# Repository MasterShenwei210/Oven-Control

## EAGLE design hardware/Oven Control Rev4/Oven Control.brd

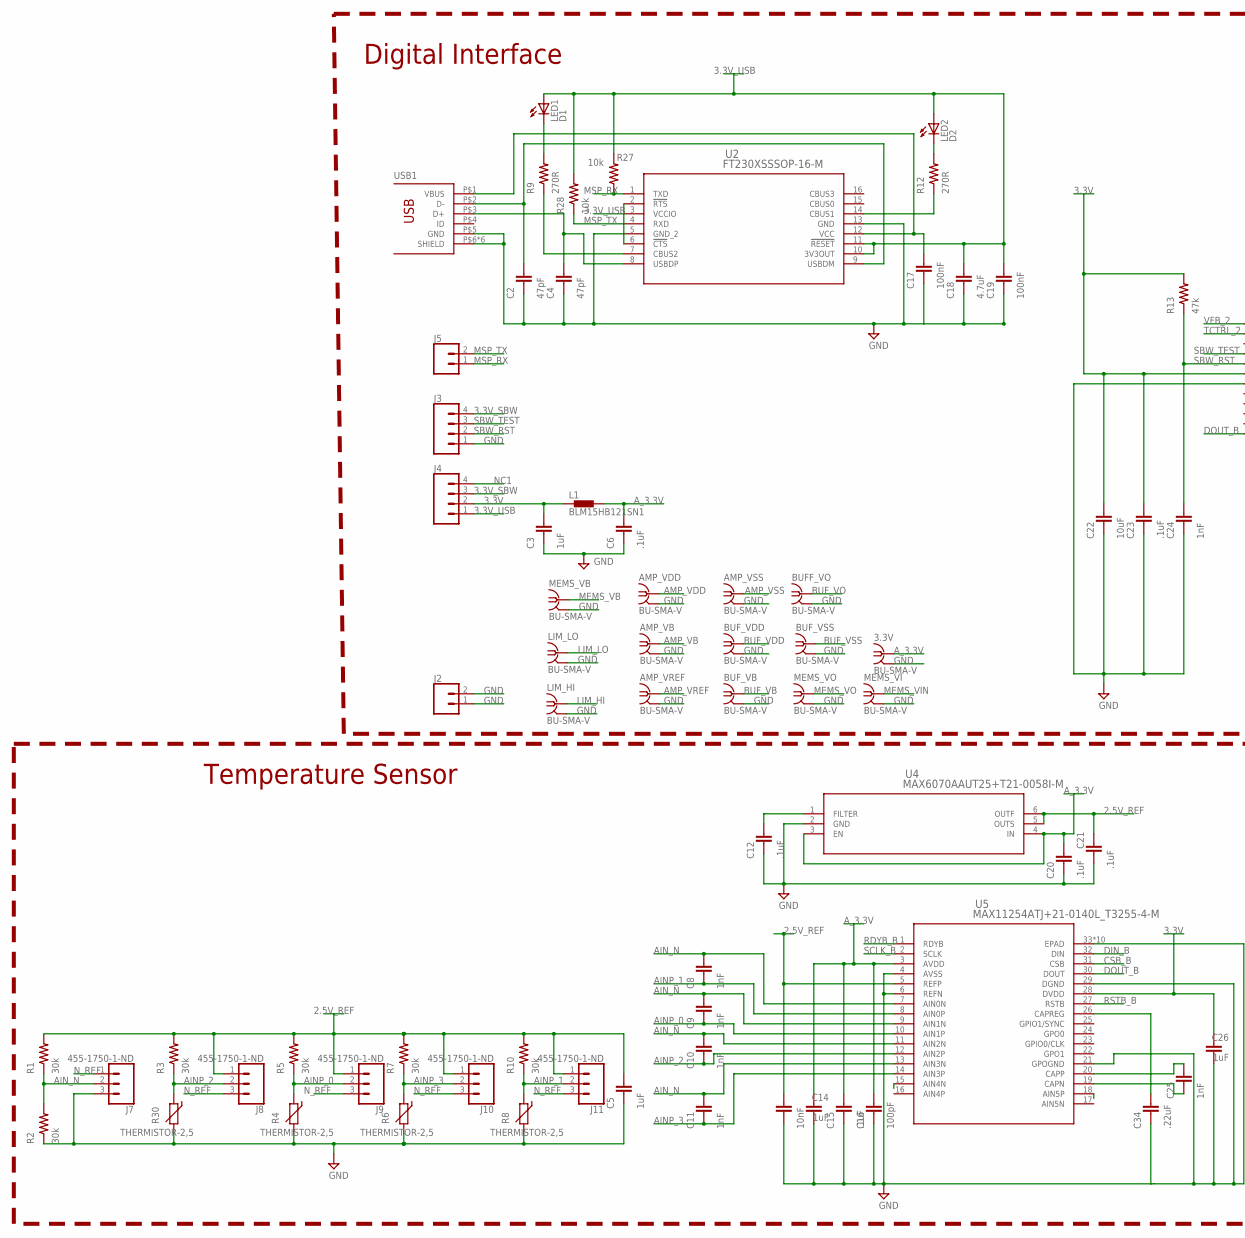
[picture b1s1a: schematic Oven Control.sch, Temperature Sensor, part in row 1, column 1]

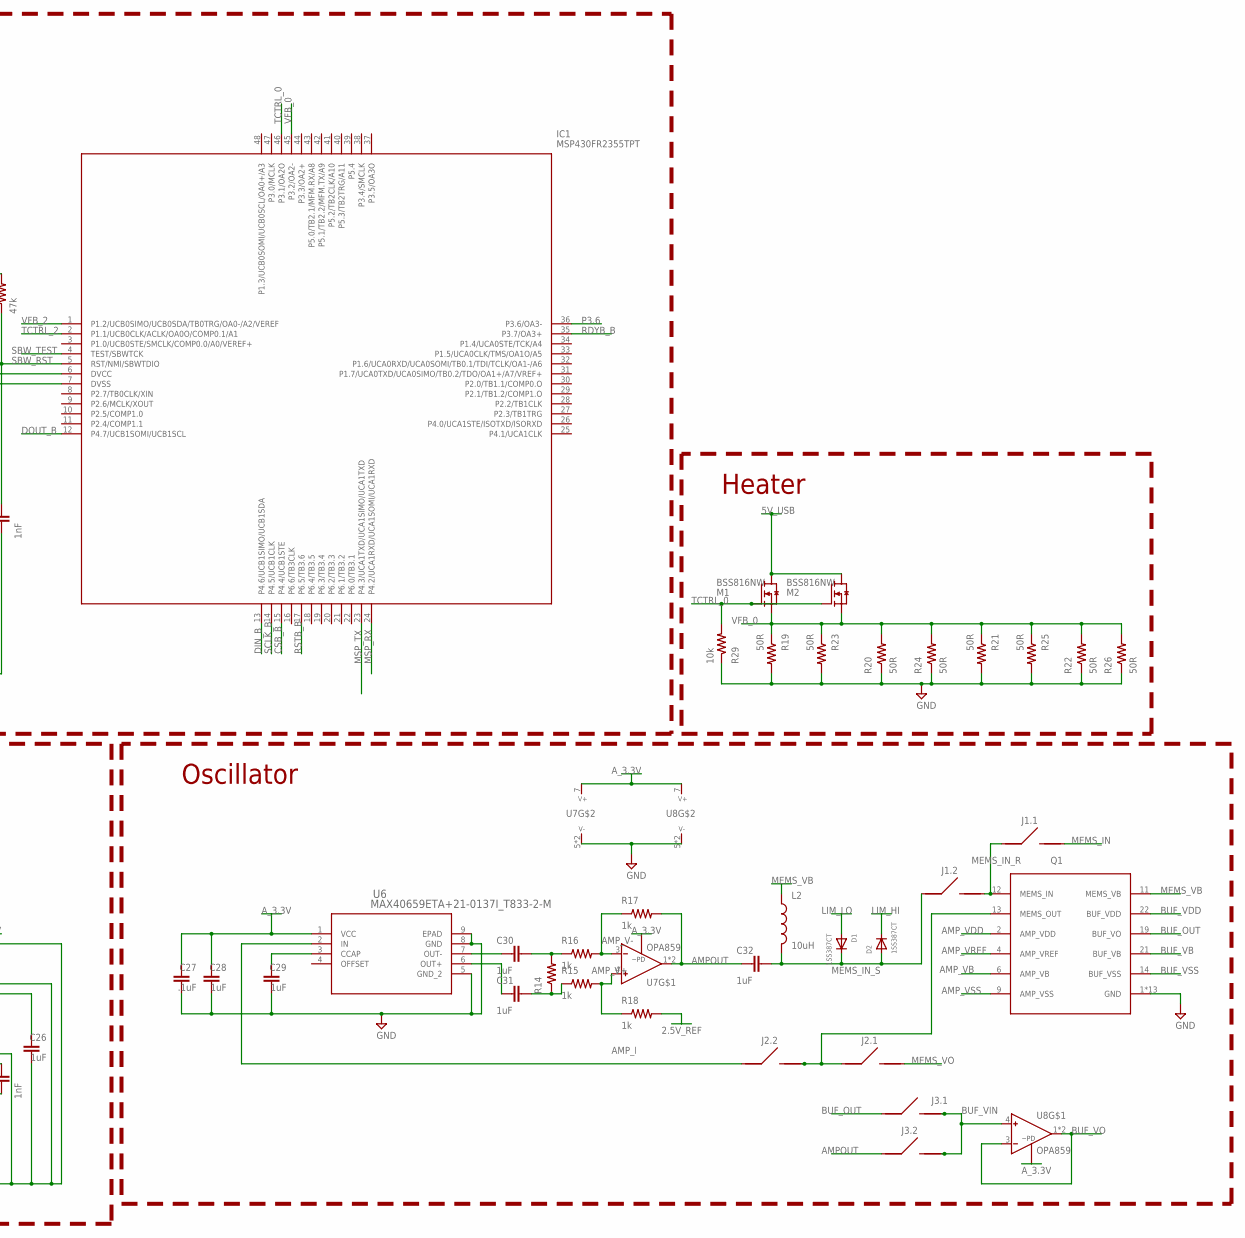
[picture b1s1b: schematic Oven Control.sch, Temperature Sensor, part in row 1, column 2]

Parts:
3.3V: BU-SMA-V
AMP_VB: BU-SMA-V
AMP_VDD: BU-SMA-V
AMP_VREF: BU-SMA-V
AMP_VSS: BU-SMA-V
BUFF_VO: BU-SMA-V
BUF_VB: BU-SMA-V
BUF_VDD: BU-SMA-V
BUF_VSS: BU-SMA-V
C2, C4: 47pF; 0402-CAP
C3, C5, C14, C26, C28, C29, C30, C31, C32: 1uF; 0402-CAP
C6, C12, C15, C20, C21, C23, C27: .1uF; 0402-CAP
C8, C9, C10, C11, C24, C25: 1nF; 0402-CAP
C13: 10nF; 0402-CAP
C16: 100pF; 0402-CAP
C17, C19: 100nF; 0402-CAP
C18: 4.7uF; 0402-CAP
C22: 10uF; 0603-CAP
C34: .22uF; 0402-CAP
D1, D2: 1SS387CT; SOD-882
IC1: MSP430FR2355TPT; QFP50P900X900X145-48N
J1.1, J1.2, J2.1, J2.2, J3.1, J3.2: 0OHM_R; R0402
J2, J5: CONN_02; 1X02
J3, J4: CONN_04; 1X04
J7, J8, J9, J10, J11: 455-1750-1-ND; 1X03
L1: BLM15HB121SN1; 0402
L2: 10uH; R0805
LED1: D1; CHIPLED_0603
LED2: D2; CHIPLED_0603
LIM_HI: BU-SMA-V
LIM_LO: BU-SMA-V
M1, M2: BSS816NW; SOT-323
MEMS_VB: BU-SMA-V
MEMS_VI: BU-SMA-V
MEMS_VO: BU-SMA-V
Q1: MEMS_RESONATOR; DIL24
R1, R2, R3, R5, R7, R10: 30k; R0603
R4, R6, R8, R30: THERMISTOR-2,5; RS-2,5; PART_NO NXRT15WB473FA1B030
R9, R12: 270R; R0603
R13: 47k; R0603
R14: 150R; R0402
R15, R16, R17, R18: 1k; R0402
R19, R20, R21, R22, R23, R24, R25, R26: 50R; R1206
R27, R28, R29: 10k; R0402
U2: FT230XSSSOP-16-M; SSOP-16-M
U4: MAX6070AAUT25+T21-0058I-M; 21-0058I-M
U5: MAX11254ATJ+21-0140L_T3255-4-M; 21-0140L_T3255-4-M
U6: MAX40659ETA+21-0137I_T833-2-M; 21-0137I_T833-2-M
U7, U8: OPA859; SON50P200X200X80-9N
USB1: USB-OTGMICRO-AB; USB-MICRO-AB

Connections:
2.5V_REF: C5.2, C13.2, C21.2, J8.1, J9.1, J10.1, J11.1, R1.2, R3.2, R5.2, R7.2, R10.2, R18.2, U4.5 (OUTS), U4.6 (OUTF), U5.5 (REFP)
3.3V: C3.2, C22.2, C23.2, C26.2, IC1.6 (DVCC), J4.2, L1.1, R13.2, U5.28 (DVDD)
3.3V_SBW: J3.4, J4.3
3.3V_USB: C18.2, C19.2, J4.1, LED1.A, LED2.A, R27.2, R28.2, U2.3 (VCCIO), U2.10 (3V3OUT), U2.11 (!RESET)
5V_USB: C17.2, M1.D, M2.D, U2.12 (VCC), USB1.P$1 (VBUS)
AINP_0: C9.1, J9.2, R4.1, R5.1, U5.10 (AIN1P)
AINP_1: C8.1, J11.2, R8.1, R10.1, U5.8 (AIN0P)
AINP_2: C10.1, J8.2, R3.1, R30.1, U5.12 (AIN2P)
AINP_3: C11.1, J10.2, R6.1, R7.1, U5.14 (AIN3P)
AIN_N: C8.2, C9.2, C10.2, C11.2, J7.2, R1.1, R2.2, U5.7 (AIN0N), U5.9 (AIN1N), U5.11 (AIN2N), U5.13 (AIN3N)
AMPOUT: C32.1, J3.2.1, R17.2, U7.1 (OUT), U7.6 (OUT)
AMP_I: J2.2.1, U6.2 (IN)
AMP_V+: R15.2, R18.1, U7.4 (IN+)
AMP_V-: R16.2, R17.1, U7.3 (IN-)
AMP_VB: AMP_VB.1, Q1.6 (AMP_VB)
AMP_VDD: AMP_VDD.1, Q1.2 (AMP_VDD)
AMP_VREF: AMP_VREF.1, Q1.4 (AMP_VREF)
AMP_VSS: AMP_VSS.1, Q1.9 (AMP_VSS)
A_3.3V: 3.3V.1, C6.2, C14.2, C15.2, C16.2, C20.2, C27.2, C28.2, L1.2, U4.3 (EN), U4.4 (IN), U5.3 (AVDD), U6.1 (VCC), U7.7 (V+), U7.8, U8.7 (V+), U8.8
BUF_OUT: J3.1.1, Q1.19 (BUF_VO)
BUF_VB: BUF_VB.1, Q1.21 (BUF_VB)
BUF_VDD: BUF_VDD.1, Q1.22 (BUF_VDD)
BUF_VIN: J3.1.2, J3.2.2, U8.4 (IN+)
BUF_VO: BUFF_VO.1, U8.1 (OUT), U8.3 (IN-), U8.6 (OUT)
BUF_VSS: BUF_VSS.1, Q1.14 (BUF_VSS)
CSB_B: IC1.15 (P4.4/UCB1STE), U5.31 (CSB)
D+: C4.2, U2.8 (USBDP), USB1.P$3 (D+)
D-: C2.2, U2.9 (USBDM), USB1.P$2 (D-)
DIN_B: IC1.13 (P4.6/UCB1SIMO/UCB1SDA), U5.32 (DIN)
DOUT_B: IC1.12 (P4.7/UCB1SOMI/UCB1SCL), U5.30 (DOUT)
GND: 3.3V.2, 3.3V.3 (2), 3.3V.4 (2), 3.3V.5 (2), AMP_VB.2, AMP_VB.3 (2), AMP_VB.4 (2), AMP_VB.5 (2), AMP_VDD.2, AMP_VDD.3 (2), AMP_VDD.4 (2), AMP_VDD.5 (2), AMP_VREF.2, AMP_VREF.3 (2), AMP_VREF.4 (2), AMP_VREF.5 (2), AMP_VSS.2, AMP_VSS.3 (2), AMP_VSS.4 (2), AMP_VSS.5 (2), BUFF_VO.2, BUFF_VO.3 (2), BUFF_VO.4 (2), BUFF_VO.5 (2), BUF_VB.2, BUF_VB.3 (2), BUF_VB.4 (2), BUF_VB.5 (2), BUF_VDD.2, BUF_VDD.3 (2), BUF_VDD.4 (2), BUF_VDD.5 (2), BUF_VSS.2, BUF_VSS.3 (2), BUF_VSS.4 (2), BUF_VSS.5 (2), C2.1, C3.1, C4.1, C5.1, C6.1, C12.1, C13.1, C14.1, C15.1, C16.1, C17.1, C18.1, C19.1, C20.1, C21.1, C22.1, C23.1, C24.1, C26.1, C27.1, C28.1, C29.1, C34.1, IC1.7 (DVSS), J2.1, J2.2, J3.1, J7.3, LIM_HI.2, LIM_HI.3 (2), LIM_HI.4 (2), LIM_HI.5 (2), LIM_LO.2, LIM_LO.3 (2), LIM_LO.4 (2), LIM_LO.5 (2), MEMS_VB.2, MEMS_VB.3 (2), MEMS_VB.4 (2), MEMS_VB.5 (2), MEMS_VI.2, MEMS_VI.3 (2), MEMS_VI.4 (2), MEMS_VI.5 (2), MEMS_VO.2, MEMS_VO.3 (2), MEMS_VO.4 (2), MEMS_VO.5 (2), Q1.1 (GND), Q1.3 (GND), Q1.5 (GND), Q1.7 (GND), Q1.8 (GND), Q1.10 (GND), Q1.15 (GND), Q1.16 (GND), Q1.17 (GND), Q1.18 (GND), Q1.20 (GND), Q1.23 (GND), Q1.24 (GND), R2.1, R4.2, R6.2, R8.2, R19.2, R20.1, R21.2, R22.1, R23.2, R24.1, R25.2, R26.1, R29.1, R30.2, U2.5 (GND_2), U2.13 (GND), U4.2 (GND), U5.4 (AVSS), U5.6 (REFN), U5.21 (GPOGND), U5.29 (DGND), U5.33 (EPAD), U5.P$1 (EPAD), U5.P$2 (EPAD), U5.P$3 (EPAD), U5.P$4 (EPAD), U5.P$5 (EPAD), U5.P$6 (EPAD), U5.P$7 (EPAD), U5.P$8 (EPAD), U5.P$9 (EPAD), U6.5 (GND_2), U6.8 (GND), U6.9 (EPAD), U7.5 (V-), U7.9 (V-), U8.5 (V-), U8.9 (V-), USB1.P$5 (GND), USB1.P$6 (SHIELD), USB1.P$7 (SHIELD), USB1.P$8 (SHIELD), USB1.P$9 (SHIELD), USB1.P$10 (SHIELD), USB1.P$11 (SHIELD)
LIM_HI: D2.C, LIM_HI.1
LIM_LO: D1.A, LIM_LO.1
MEMS_IN: J1.1.2
MEMS_IN_R: J1.1.1, J1.2.2, Q1.12 (MEMS_IN)
MEMS_IN_S: C32.2, D1.C, D2.A, J1.2.1, L2.2
MEMS_OUT: J2.1.1, J2.2.2, Q1.13 (MEMS_OUT)
MEMS_VB: L2.1, MEMS_VB.1, Q1.11 (MEMS_VB)
MEMS_VIN: MEMS_VI.1
MEMS_VO: J2.1.2, MEMS_VO.1
MSP_RX: IC1.24 (P4.2/UCA1RXD/UCA1SOMI/UCA1RXD), J5.1, R27.1, U2.1 (TXD)
MSP_TX: IC1.23 (P4.3/UCA1TXD/UCA1SIMO/UCA1TXD), J5.2, R28.1, U2.4 (RXD)
unnamed: C25.2, U5.20 (CAPP)
unnamed: C25.1, U5.19 (CAPN)
unnamed: C31.2, R14.1, R15.1
unnamed: C29.2, U6.3 (CCAP)
unnamed: C12.2, U4.1 (FILTER)
unnamed: C30.2, R14.2, R16.1
unnamed: C34.2, U5.26 (CAPREG)
unnamed: C30.1, U6.7 (OUT-)
unnamed: C31.1, U6.6 (OUT+)
unnamed: U2.2 (!RTS), U2.6 (!CTS)
unnamed: LED2.C, R12.2
unnamed: LED1.C, R9.2
NC1: J4.4
N_REF: J7.1, J8.3, J9.3, J10.3, J11.3
P3.6: IC1.36 (P3.6/OA3-)
RDYB_B: IC1.35 (P3.7/OA3+), U5.1 (RDYB)
RSTB_B: IC1.17 (P6.5/TB3.6), U5.27 (RSTB)
RX#1: R12.1, U2.14 (CBUS1)
SBW_RST: C24.2, IC1.5 (RST/NMI/SBWTDIO), J3.2, R13.1
SBW_TEST: IC1.4 (TEST/SBWTCK), J3.3
SCLK_B: IC1.14 (P4.5/UCB1CLK), U5.2 (SCLK)
TCTRL_0: IC1.46 (P3.1/OA2O), M1.G, M2.G, R29.2
TCTRL_2: IC1.2 (P1.1/UCB0CLK/ACLK/OA0O/COMP0.1/A1)
TX#1: R9.1, U2.7 (CBUS2)
VFB_0: IC1.45 (P3.2/OA2-), M1.S, M2.S, R19.1, R20.2, R21.1, R22.2, R23.1, R24.2, R25.1, R26.2
VFB_2: IC1.1 (P1.2/UCB0SIMO/UCB0SDA/TB0TRG/OA0-/A2/VE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)

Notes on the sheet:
Temperature Sensor
Digital Interface
Heater
Oscillator

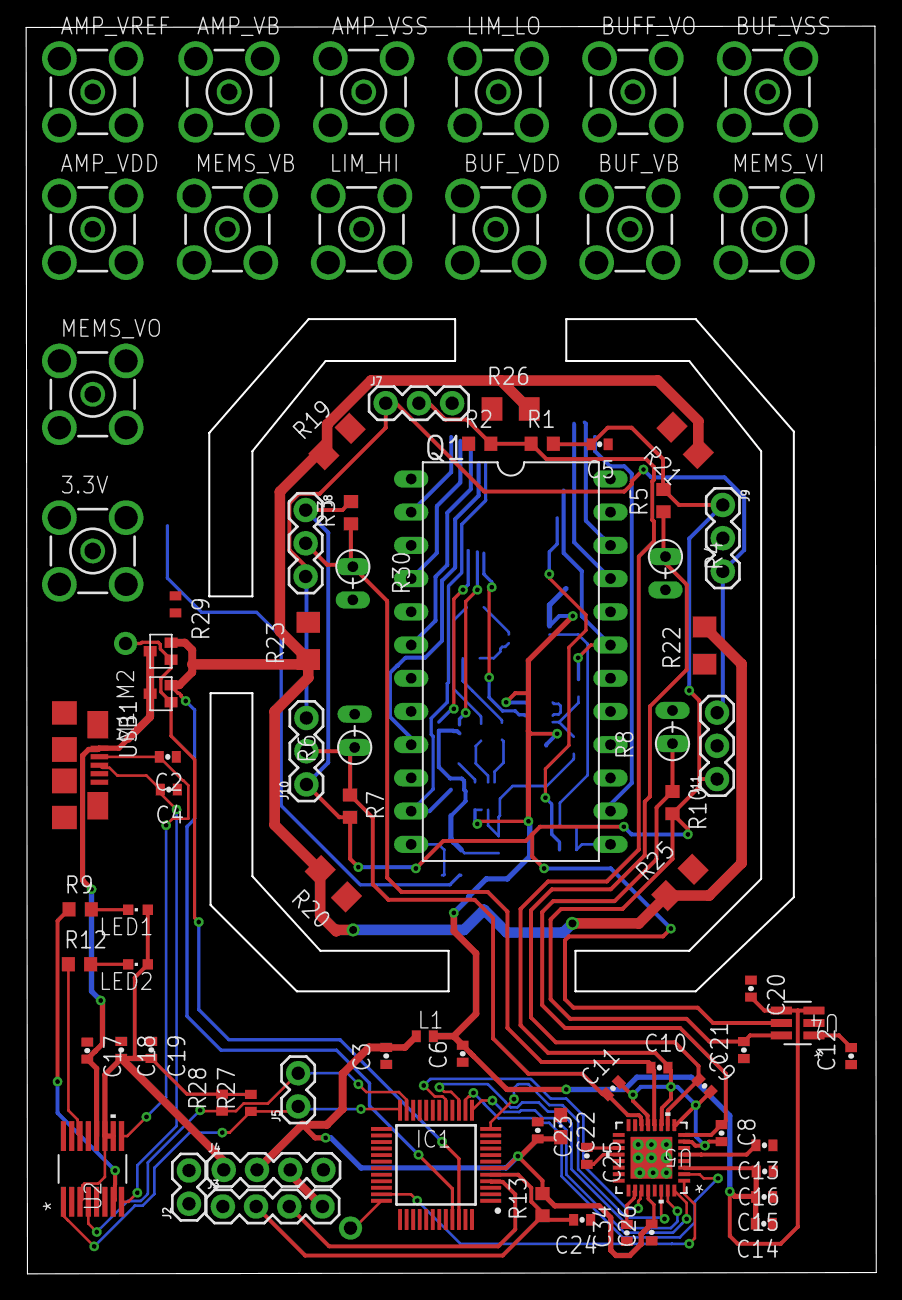
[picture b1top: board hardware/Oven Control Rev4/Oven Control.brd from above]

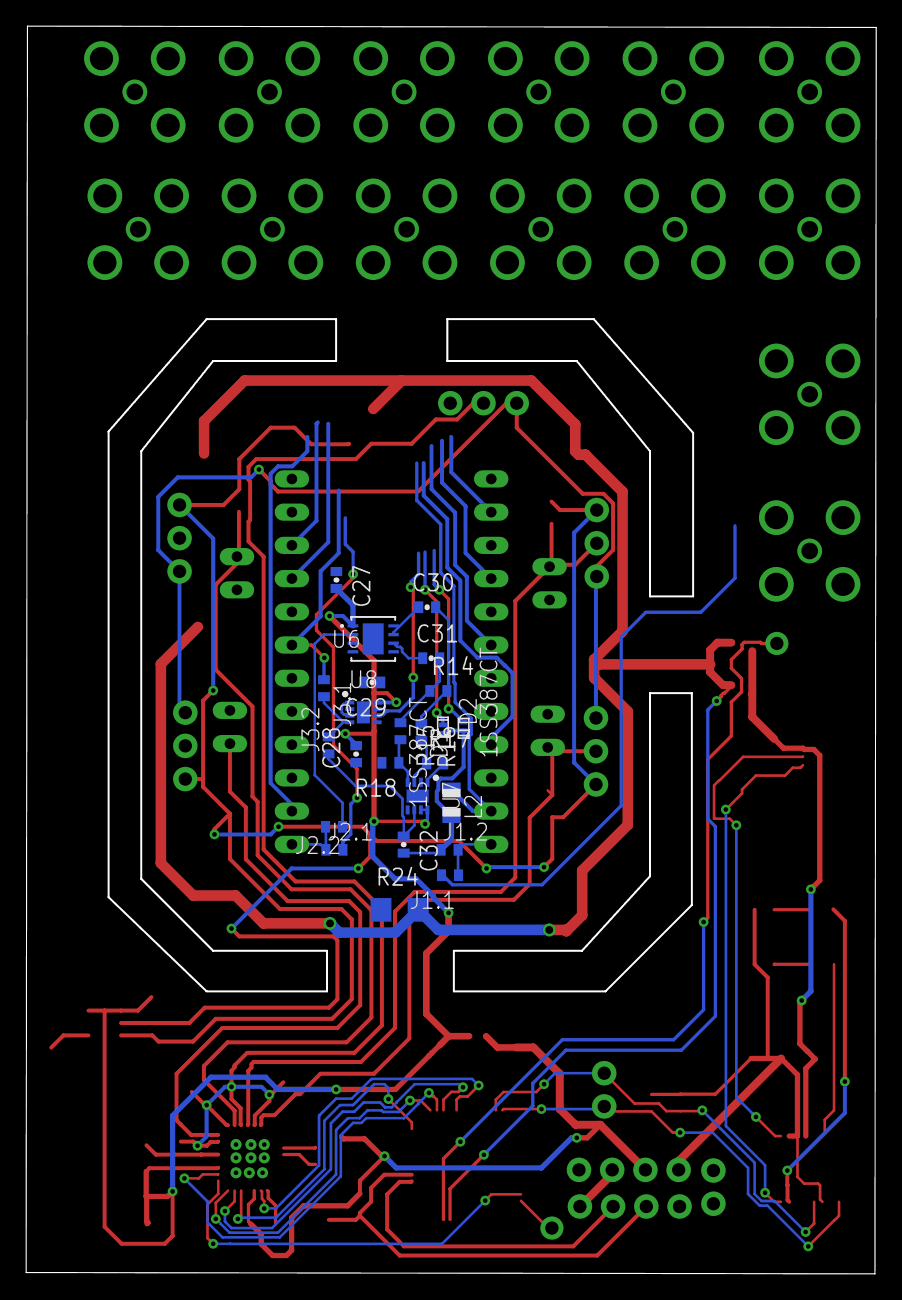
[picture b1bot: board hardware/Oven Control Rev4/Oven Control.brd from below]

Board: 2 copper layers, 65.0 x 95.4 mm, 106 parts (24 on the bottom side), 62 nets.

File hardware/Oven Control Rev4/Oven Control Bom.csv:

"Qty";"Value";"Device";"Package";"Parts";"Description";"DESCRIPTION";"DISTRIBUTOR";"DISTRIBUTOR_PART_NUMBER";"HEIGHT";"MANUFACTURER";"MANUFACTURER_NAME";"MANUFACTURER_PART_NUMBER";"MOUSER_PART_NUMBER";"MOUSER_PRICE-STOCK";"NOTES";"PACKAGE";"PIE-DIGIKEY-PN-PRI";"PIE-INT-REF-NUM";"PROD_ID";"VALUE";"VENDOR";
"1";"";"CONN_02";"1X02";"J2";"Multi connection point. Often used as Generic Header-pin footprint for 0.1 inch spaced/style header connections";"";"";"";"";"";"";"";"";"";"";"";"";"";"";"";"";
"2";"";"CONN_04";"1X04";"J3, J4";"Multi connection point. Often used as Generic Header-pin footprint for 0.1 inch spaced/style header connections";"";"";"";"";"";"";"";"";"";"";"";"";"";"CONN-09696";"";"";
"4";"";"R-US_R1206";"R1206";"R19, R20, R21, R22";"RESISTOR, American symbol";"";"";"";"";"";"";"";"";"";"";"";"";"RESISTOR-GENERIC";"";"";"";
"7";".1uF";"CAP0402-CAP";"0402-CAP";"C6, C12, C15, C20, C21, C23, C27";"Capacitor";"";"";"";"";"";"";"";"";"";"";"";"";"CAPACITOR-GENERIC";"";"";"";
"2";"100nF";"CAP0402-CAP";"0402-CAP";"C17, C19";"Capacitor";"";"";"";"";"";"";"";"";"";"";"";"";"CAPACITOR-GENERIC";"";"";"";
"1";"100pF";"CAP0402-CAP";"0402-CAP";"C16";"Capacitor";"";"";"";"";"";"";"";"";"";"";"";"";"CAPACITOR-GENERIC";"";"";"";
"1";"10nF";"CAP0402-CAP";"0402-CAP";"C13";"Capacitor";"";"";"";"";"";"";"";"";"";"";"";"";"CAPACITOR-GENERIC";"";"";"";
"1";"10uF";"CAP0603-CAP";"0603-CAP";"C22";"Capacitor";"";"";"";"";"";"";"";"";"";"";"";"";"CAPACITOR-GENERIC";"";"";"";
"1";"150R";"R-US_R0402";"R0402";"R14";"RESISTOR, American symbol";"";"";"";"";"";"";"";"";"";"";"";"";"RESISTOR-GENERIC";"";"";"";
"6";"1nF";"CAP0402-CAP";"0402-CAP";"C8, C9, C10, C11, C24, C25";"Capacitor";"";"";"";"";"";"";"";"";"";"";"";"";"CAPACITOR-GENERIC";"";"";"";
"10";"1uF";"CAP0402-CAP";"0402-CAP";"C1, C3, C5, C7, C14, C26, C28, C29, C30, C31";"Capacitor";"";"";"";"";"";"";"";"";"";"";"";"";"CAPACITOR-GENERIC";"";"";"";
"4";"21k";"R-US_R0402";"R0402";"R15, R16, R17, R18";"RESISTOR, American symbol";"";"";"";"";"";"";"";"";"";"";"";"";"RESISTOR-GENERIC";"";"";"";
"2";"270R";"R-US_R0603";"R0603";"R9, R12";"RESISTOR, American symbol";"RESISTOR, American symbol";"DigiKey";"";"";"Rohm Semiconductor";"";"";"";"";"Cut Tape";"R0603";"";"";"";">VALUE";"";
"6";"30k";"R-US_R0603";"R0603";"R1, R2, R3, R5, R7, R10";"RESISTOR, American symbol";"RESISTOR, American symbol";"DigiKey";"";"";"Rohm Semiconductor";"";"";"";"";"Cut Tape";"R0603";"";"";"";">VALUE";"";
"1";"4.7uF";"CAP0402-CAP";"0402-CAP";"C18";"Capacitor";"";"";"";"";"";"";"";"";"";"";"";"";"CAPACITOR-GENERIC";"";"";"";
"1";"455-1750-1-ND";"CONN_03";"1X03";"J1";"Multi connection point. Often used as Generic Header-pin footprint for 0.1 inch spaced/style header connections";"";"";"";"";"";"";"";"";"";"";"";"";"";"XXX-00000";"455-1750-1-ND";"";
"1";"47k";"R-US_R0402";"R0402";"R13";"RESISTOR, American symbol";"";"";"";"";"";"";"";"";"";"";"";"";"RESISTOR-GENERIC";"";"";"";
"4";"47k";"R-US_R0603";"R0603";"R4, R6, R8, R11";"RESISTOR, American symbol";"RESISTOR, American symbol";"DigiKey";"";"";"Rohm Semiconductor";"";"";"";"";"Cut Tape";"R0603";"";"";"";">VALUE";"";
"2";"47pF";"CAP0402-CAP";"0402-CAP";"C2, C4";"Capacitor";"";"";"";"";"";"";"";"";"";"";"";"";"CAPACITOR-GENERIC";"";"";"";
"1";"BLM15HB121SN1";"BLM15HB121SN1";"0402";"L1";"EMIFIL (R) Chip Ferrite Bead for GHz Noise";"";"";"";"";"";"";"";"";"";"";"";"";"";"";"";"";
"4";"BSS816NW";"BSS816NW";"SOT-323";"M1, M2, M3, M4";"";"";"";"";"";"";"";"";"";"";"";"";"";"";"";"";"";
"1";"D1";"LEDCHIPLED_0603";"CHIPLED_0603";"LED1";"LED";"";"";"";"";"";"";"";"";"";"";"";"";"";"";"";"";
"1";"D2";"LEDCHIPLED_0603";"CHIPLED_0603";"LED2";"LED";"";"";"";"";"";"";"";"";"";"";"";"";"";"";"";"";
"1";"FT230XSSSOP-16-M";"FT230XSSSOP-16-M";"SSOP-16-M";"U2";"";"";"";"";"";"";"";"FT230XS";"";"";"";"";"";"";"";"";"FTDI Future Technology Devices International Ltd";
"1";"LTC6253";"LTC6253";"DFN";"U7";"";"";"";"";"";"";"";"";"";"";"";"";"";"";"";"";"";
"1";"MAX11254ATJ+21-0140L_T3255-4-M";"MAX11254ATJ+21-0140L_T3255-4-M";"21-0140L_T3255-4-M";"U5";"";"";"";"";"";"";"";"MAX11254ATJ+";"";"";"";"";"";"";"";"";"Maxim Integrated Products";
"1";"MAX40659ETA+21-0137I_T833-2-M";"MAX40659ETA+21-0137I_T833-2-M";"21-0137I_T833-2-M";"U6";"";"";"";"";"";"";"";"MAX40659ETA+";"";"";"";"";"";"";"";"";"Maxim Integrated Products";
"1";"MAX6070AAUT25+T21-0058I-M";"MAX6070AAUT25+T21-0058I-M";"21-0058I-M";"U4";"";"";"";"";"";"";"";"MAX6070AAUT25+T";"";"";"";"";"";"";"";"";"Maxim Integrated Products";
"1";"MEMS_RESONATOR";"MEMS_RESONATOR";"DIL24";"Q1";"";"";"";"";"";"";"";"";"";"";"";"";"";"";"";"";"";
"1";"MIC5504";"MIC5504";"DBV6-M";"U1";"";"";"";"";"";"";"";"";"";"";"";"";"";"";"";"";"";
"1";"MSP430FR2355TPT";"MSP430FR2355TPT";"QFP50P900X900X145-48N";"IC1";"16-bit Microcontrollers - MCU 24MHz 105C ULP Microcontroller With 32 KB FRAM, 4 KB SRAM, 44 IO, 12-bit ADC, 12-bit DACs, OpAmp/PGA 48-LQFP -40 to 105";"16-bit Microcontrollers - MCU 24MHz 105C ULP Microcontroller With 32 KB FRAM, 4 KB SRAM, 44 IO, 12-bit ADC, 12-bit DACs, OpAmp/PGA 48-LQFP -40 to 105";"";"";"1.45mm";"";"Texas Instruments";"MSP430FR2355TPT";"";"";"";"";"";"";"";"";"";
"1";"TXB0106PWRPW16-M";"TXB0106PWRPW16-M";"PW16-M";"U3";"";"";"";"";"";"";"";"TXB0106PWR";"";"";"";"";"";"";"";"";"Texas Instruments";
"1";"USB-OTGMICRO-AB";"USB-OTGMICRO-AB";"USB-MICRO-AB";"USB1";"USB Connector";"";"";"";"";"";"";"";"";"";"";"";"H11635CT-ND";"USB";"";"";"";

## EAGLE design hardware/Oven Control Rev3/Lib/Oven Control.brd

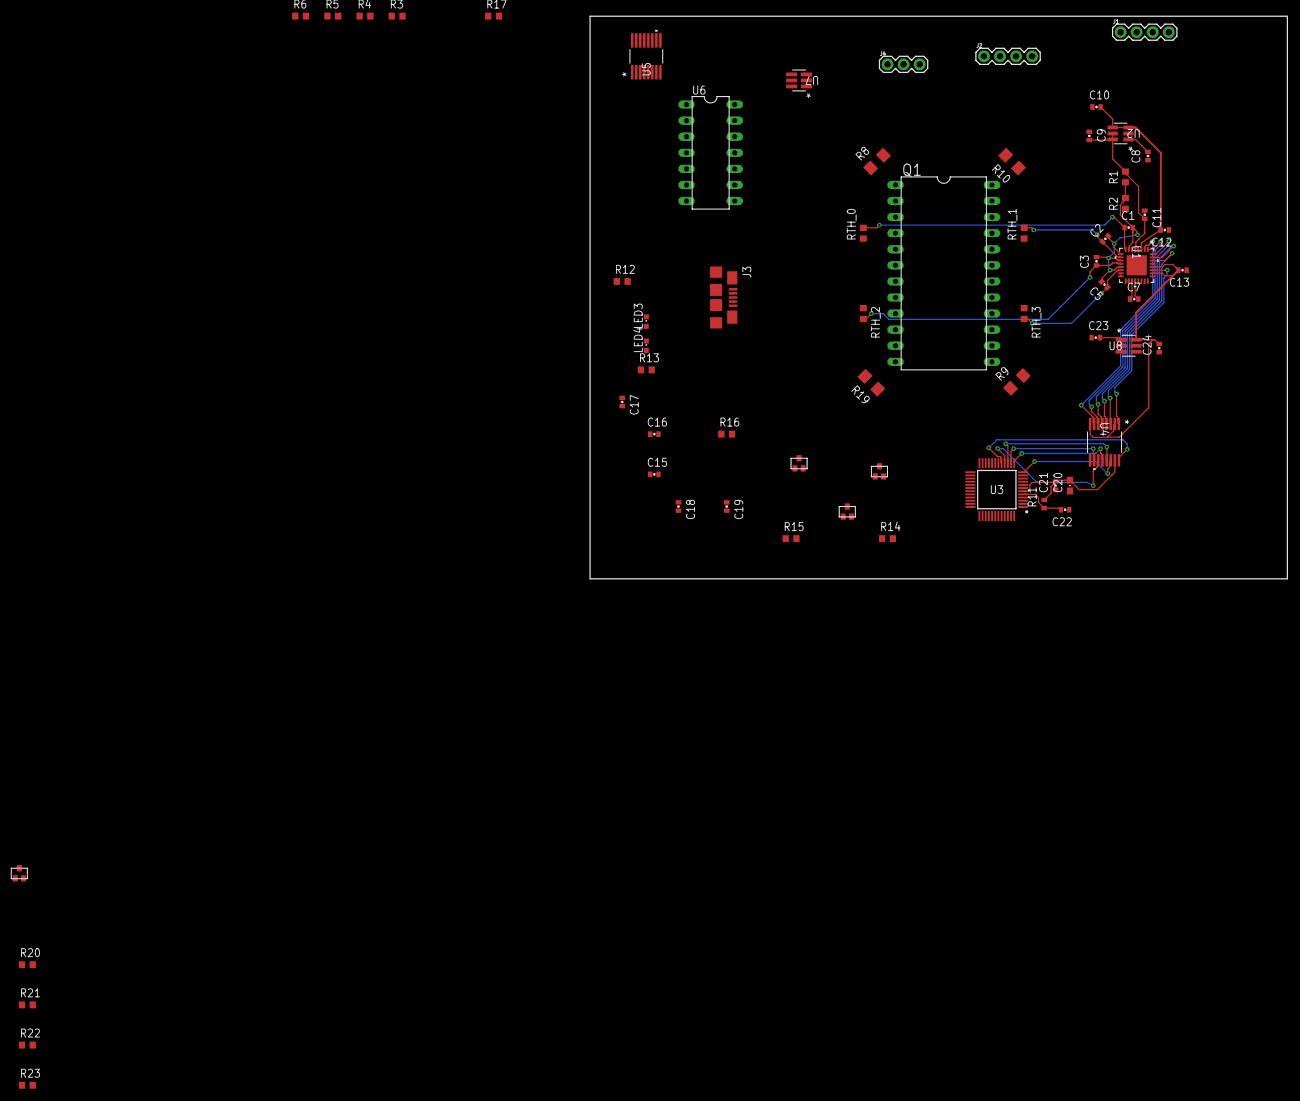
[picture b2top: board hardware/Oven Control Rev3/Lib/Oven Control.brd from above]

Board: 2 copper layers, 110.2 x 88.9 mm, 65 parts (0 on the bottom side), 60 nets.

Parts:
C1, C2, C3, C5, C7, C22: 1nF; 0402-CAP
C8, C9, C10, C21: .1uF; 0402-CAP
C11: 10nF; 0402-CAP
C12, C13, C23, C24: 1uF; 0402-CAP
C15, C16: 47pF; 0402-CAP
C17, C19: 100nF; 0402-CAP
C18: 4.7uF; 0402-CAP
C20: 10uF; 0603-CAP
J1, J2: 1X04
J3: USB-OTGMICRO-AB; USB-MICRO-AB
J4: 455-1750-1-ND; 1X03
LED3: D2; CHIPLED_0603
LED4: D1; CHIPLED_0603
M1, M2, M3, M4: BSS816NW; SOT-323
Q1: MEMS_RESONATOR; DIL24
R1, R2, R3, R4, R5, R6: 30k; R0603
R8, R9, R10, R19: R1206
R11: 47k; R0402
R12, R13: 270R; R0603
R14, R15, R16, R17: 21k; R0603
R20, R21, R22, R23: >VALUE; R0603
RTH_0, RTH_1, RTH_2, RTH_3: 47k; R0603
U1: MAX11254ATJ+21-0140L_T3255-4-M; 21-0140L_T3255-4-M
U2: MAX6070AAUT25+T21-0058I-M; 21-0058I-M
U3: MSP430FR2355TPT; QFP50P900X900X145-48N
U4: TXB0106PWRPW16-M; PW16-M
U5: FT230XSSSOP-16-M; SSOP-16-M
U6: NE5211; DIL14
U7: OPA322AIDBVRDBV6-M; DBV6-M
U8: MIC5504; DBV6-M

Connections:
1.8V: C13.2, C24.2, U1.26, U1.28, U4.2, U4.8, U8.6
2.5V_REF: C9.2, C11.2, R1.2, R3.2, R4.2, R5.2, R6.2, U1.5, U2.5, U2.6
3.3V: C10.2, C12.2, C20.2, C21.2, C23.2, J2.2, R11.2, U1.3, U2.3, U2.4, U3.6, U4.15, U8.1
3.3V_SBW: J1.4, J2.3
3.3V_USB: C18.2, C19.2, J2.1, LED3.A, LED4.A, U5.3, U5.10, U5.11
5V: J4.2, R8.2, R9.2, R10.2, R19.2, U6.6, U6.7, U7.6
5V_USB: C17.2, J3.P$1, J4.3, U5.12
AINP_0: C1.1, R3.1, RTH_0.2, U1.8
AINP_1: C2.1, R4.1, RTH_1.2, U1.10
AINP_2: C3.1, R5.1, RTH_2.2, U1.12
AINP_3: C5.1, R6.1, RTH_3.2, U1.14
AIN_N: C1.2, C2.2, C3.2, C5.2, R1.1, R2.2, U1.7, U1.9, U1.11, U1.13
CSB: U1.31, U4.4
CSB_B: U3.15, U4.13
D+: C16.2, J3.P$3, U5.8
D-: C15.2, J3.P$2, U5.9
DIN: U1.32, U4.5
DIN_B: U3.13, U4.12
DOUT: U1.30, U4.3
DOUT_B: U3.12, U4.14
GND: C8.1, C9.1, C10.1, C11.1, C12.1, C13.1, C15.1, C16.1, C17.1, C18.1, C19.1, C20.1, C21.1, C22.1, C23.1, C24.1, J1.1, J3.P$5, J3.P$6, J3.P$7, J3.P$8, J3.P$9, J3.P$10, J3.P$11, R2.1, RTH_0.1, RTH_1.1, RTH_2.1, RTH_3.1, U1.4, U1.6, U1.21, U1.29, U1.33, U2.2, U3.7, U4.9, U5.5, U5.13, U6.1, U6.2, U6.8, U6.9, U6.10, U6.11, U6.13, U7.2, U8.2
MSP_RX: U3.24, U5.1
MSP_TX: U3.23, U5.4
unnamed: C7.2, U1.20
unnamed: C7.1, U1.19
unnamed: M1.D, R8.1
unnamed: R17.1, U6.14
unnamed: M1.S, R20.2
unnamed: C8.2, U2.1
unnamed: M2.D, R9.1
unnamed: R16.1, U6.12
unnamed: R14.1, R17.2, U7.3
unnamed: R15.1, R16.2, U7.4
unnamed: Q1.1, Q1.2, Q1.3, Q1.4, Q1.5, Q1.6, Q1.7, Q1.8, Q1.9, Q1.10, Q1.11, Q1.12, R14.2, R15.2, U7.1
unnamed: LED3.C, R13.2
unnamed: LED4.C, R12.2
unnamed: Q1.13, Q1.14, Q1.15, Q1.16, Q1.17, Q1.18, Q1.19, Q1.20, Q1.21, Q1.22, Q1.23, Q1.24, U6.4
unnamed: M3.D, R10.1
unnamed: M4.D, R19.1
unnamed: M2.S, R21.2
unnamed: M3.S, R22.2
unnamed: M4.S, R23.2
unnamed: R20.1, R21.1, R22.1, R23.1
unnamed: U1.17, U1.18
unnamed: U1.15, U1.16
NC: J2.4, J4.1
RDYB: U1.1, U4.6
RDYB_B: U3.16, U4.11
RSTB: U1.27, U4.1
RSTB_B: U3.17, U4.16
RX#1: R13.1, U5.14
SBW_RST: C22.2, J1.2, R11.1, U3.5
SBW_TEST: J1.3, U3.4
SCLK: U1.2, U4.7
SCLK_B: U3.14, U4.10
TCTRL_0: M1.G, U3.46
TCTRL_1: M2.G, U3.37
TCTRL_2: M3.G, U3.2
TCTRL_3: M4.G, U3.33
TX#1: R12.1, U5.7

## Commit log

2019-06-12 updated spi lib
2019-06-12 made directory for application
2019-06-14 did thinkgs
2019-06-19 firmwayweht iowjebt o
2019-06-22 things
2019-06-24 yeet
2019-07-01 thinihgnin

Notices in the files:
parts and their libraries:
SparkFun-Connectors: Licensing: Creative Commons ShareAlike 4.0 International - https://creativecommons.org/licenses/by-sa/4.0
